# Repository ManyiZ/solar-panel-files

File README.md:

# About
Solar panel designs. HS-2 is designed in KiCAD, older designs are imported files from EasyEDA.

## KiCad Resources
Download: https://www.kicad.org/download/

Docs: https://docs.kicad.org/#_getting_started

## Easy EDA PCB Ordering Resource
https://docs.easyeda.com/en/PCB/Order-PCB

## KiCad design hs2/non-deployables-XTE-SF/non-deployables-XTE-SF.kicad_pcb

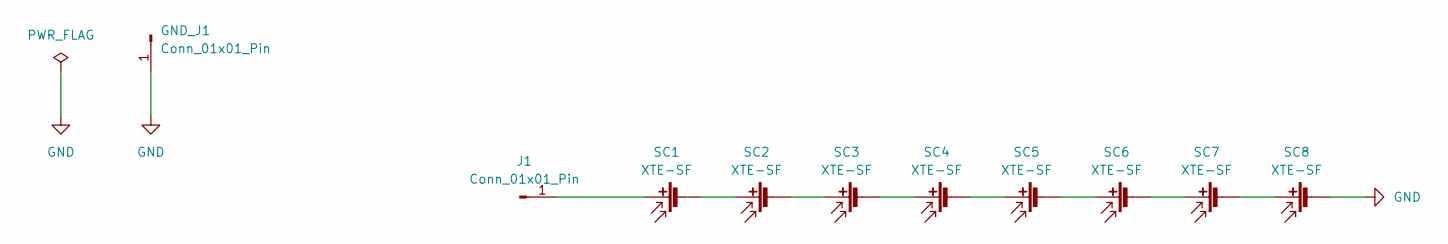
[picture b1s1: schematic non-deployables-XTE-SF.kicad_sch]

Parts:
GND_J1: Conn_01x01_Pin; SolderWirePad_1x01_SMD_5x10mm
J1: Conn_01x01_Pin; SolderWirePad_1x01_SMD_5x10mm
SC1, SC2, SC3, SC4, SC5, SC6, SC7, SC8: XTE-SF; xte-sf

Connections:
GND: GND_J1.1, SC8.2 (-)
unnamed: J1.1, SC1.1 (+)
unnamed: SC1.2 (-), SC2.1 (+)
unnamed: SC2.2 (-), SC3.1 (+)
unnamed: SC3.2 (-), SC4.1 (+)
unnamed: SC4.2 (-), SC5.1 (+)
unnamed: SC5.2 (-), SC6.1 (+)
unnamed: SC6.2 (-), SC7.1 (+)
unnamed: SC7.2 (-), SC8.1 (+)

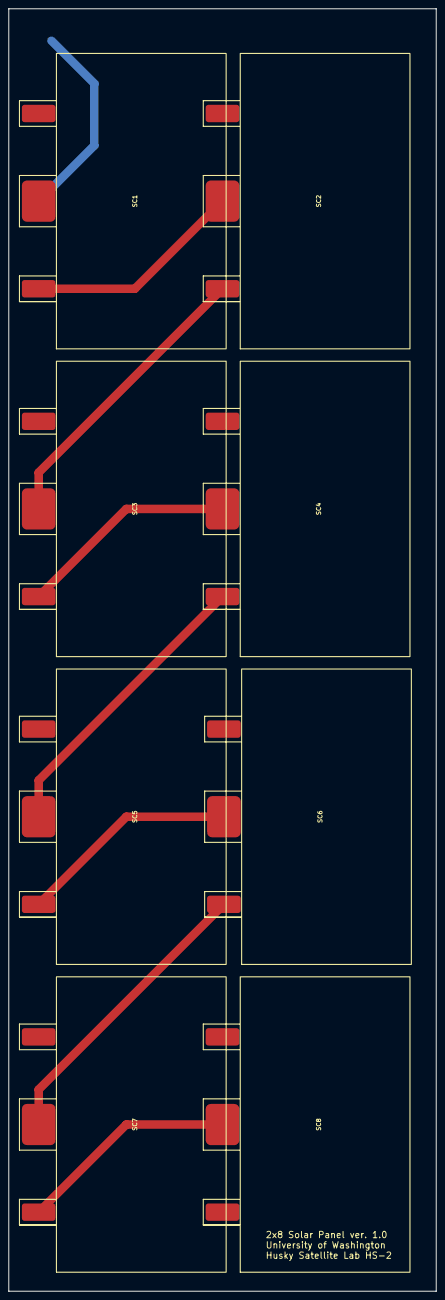
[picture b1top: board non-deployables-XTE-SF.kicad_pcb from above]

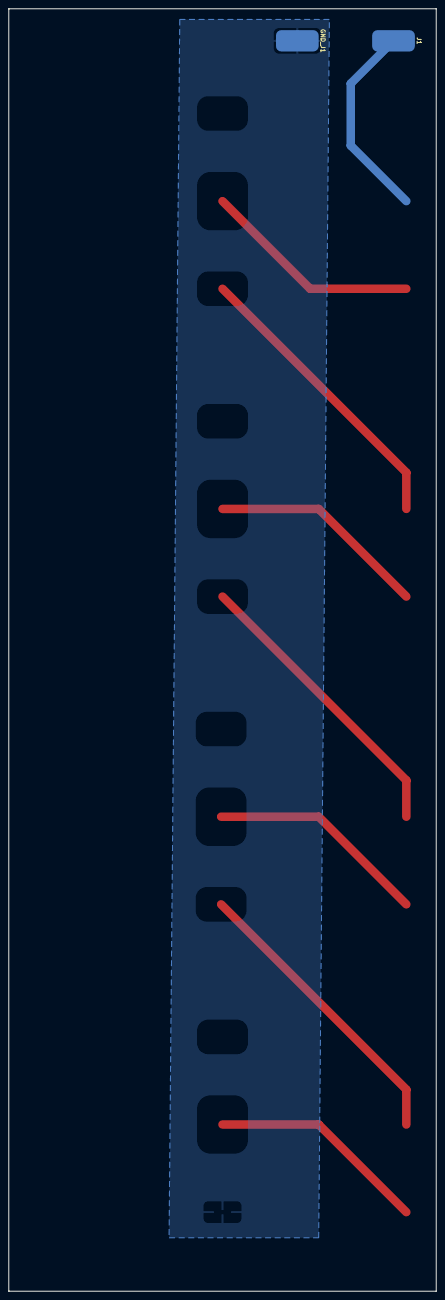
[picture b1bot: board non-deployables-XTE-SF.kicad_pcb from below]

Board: 2 copper layers, 100.0 x 300.0 mm, 10 parts (2 on the bottom side), 9 nets.

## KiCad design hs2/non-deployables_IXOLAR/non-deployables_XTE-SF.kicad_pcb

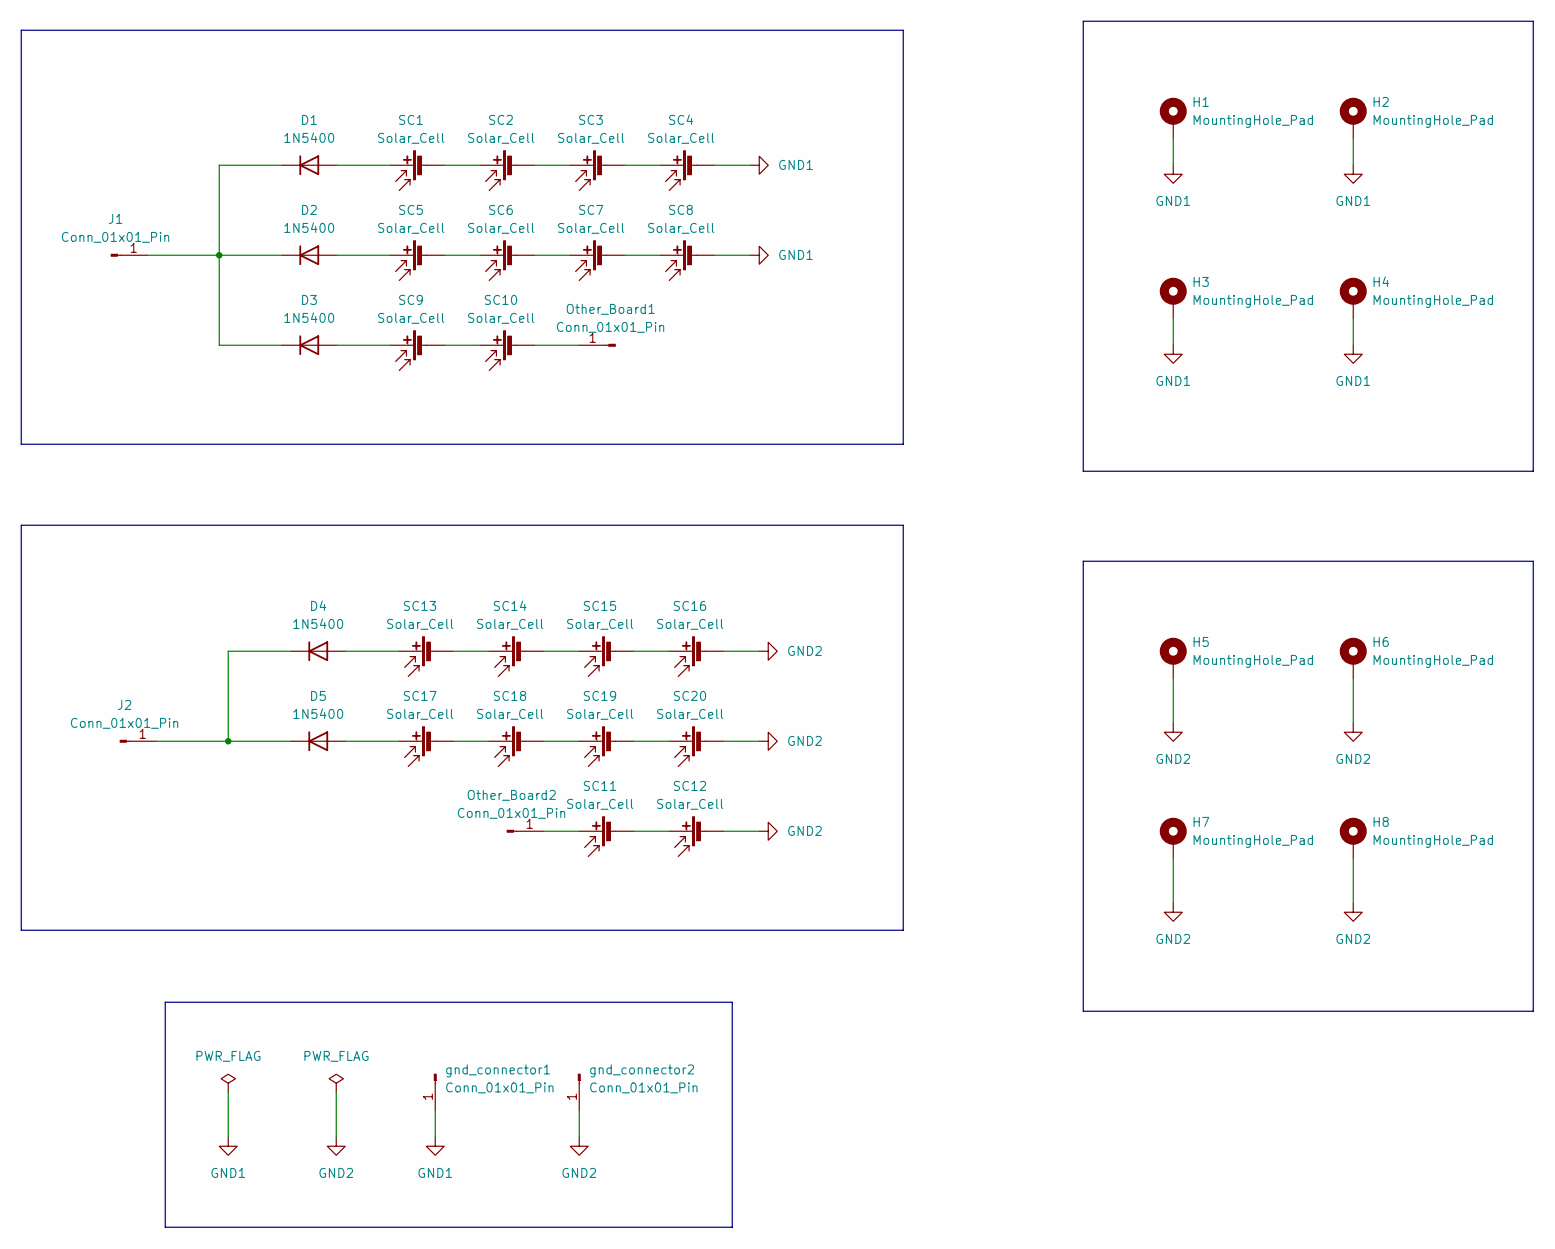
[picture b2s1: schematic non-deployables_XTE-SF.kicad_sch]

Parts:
D1, D2, D3, D4, D5: 1N5400; D_DO-201AD_P15.24mm_Horizontal
H1, H2, H3, H4, H5, H6, H7, H8: MountingHole_Pad; MountingHole_3.2mm_M3_DIN965_Pad
J1, J2: Conn_01x01_Pin; SolderWirePad_1x01_SMD_5x10mm
Other_Board1, Other_Board2: Conn_01x01_Pin; SolderWirePad_1x01_SMD_5x10mm
SC1, SC2, SC3, SC4, SC5, SC6, SC7, SC8, SC9, SC10, SC11, SC12, SC13, SC14, SC15, SC16, SC17, SC18, SC19, SC20: Solar_Cell; XOLAR_SM401K08TF
gnd_connector1, gnd_connector2: Conn_01x01_Pin; SolderWirePad_1x01_SMD_5x10mm

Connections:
GND1: H1.1, H2.1, H3.1, H4.1, SC4.2 (-), SC8.2 (-), gnd_connector1.1
GND2: H5.1, H6.1, H7.1, H8.1, SC12.2 (-), SC16.2 (-), SC20.2 (-), gnd_connector2.1
unnamed: D1.2 (A), SC1.1 (+)
unnamed: D1.1 (K), D2.1 (K), D3.1 (K), J1.1
unnamed: D2.2 (A), SC5.1 (+)
unnamed: D3.2 (A), SC9.1 (+)
unnamed: D4.2 (A), SC13.1 (+)
unnamed: D4.1 (K), D5.1 (K), J2.1
unnamed: D5.2 (A), SC17.1 (+)
unnamed: Other_Board1.1, SC10.2 (-)
unnamed: Other_Board2.1, SC11.1 (+)
unnamed: SC1.2 (-), SC2.1 (+)
unnamed: SC2.2 (-), SC3.1 (+)
unnamed: SC3.2 (-), SC4.1 (+)
unnamed: SC5.2 (-), SC6.1 (+)
unnamed: SC6.2 (-), SC7.1 (+)
unnamed: SC7.2 (-), SC8.1 (+)
unnamed: SC9.2 (-), SC10.1 (+)
unnamed: SC11.2 (-), SC12.1 (+)
unnamed: SC13.2 (-), SC14.1 (+)
unnamed: SC14.2 (-), SC15.1 (+)
unnamed: SC15.2 (-), SC16.1 (+)
unnamed: SC17.2 (-), SC18.1 (+)
unnamed: SC18.2 (-), SC19.1 (+)
unnamed: SC19.2 (-), SC20.1 (+)

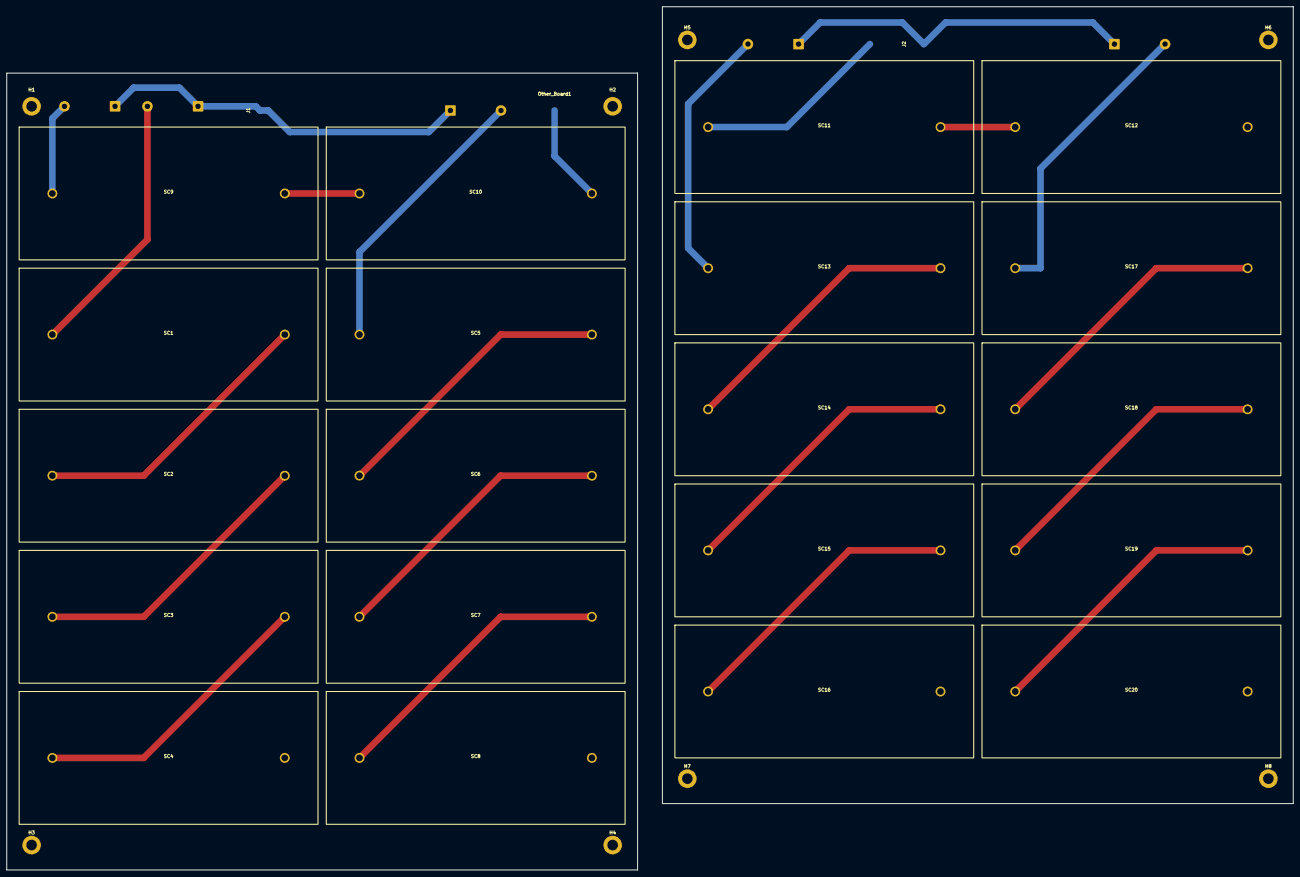
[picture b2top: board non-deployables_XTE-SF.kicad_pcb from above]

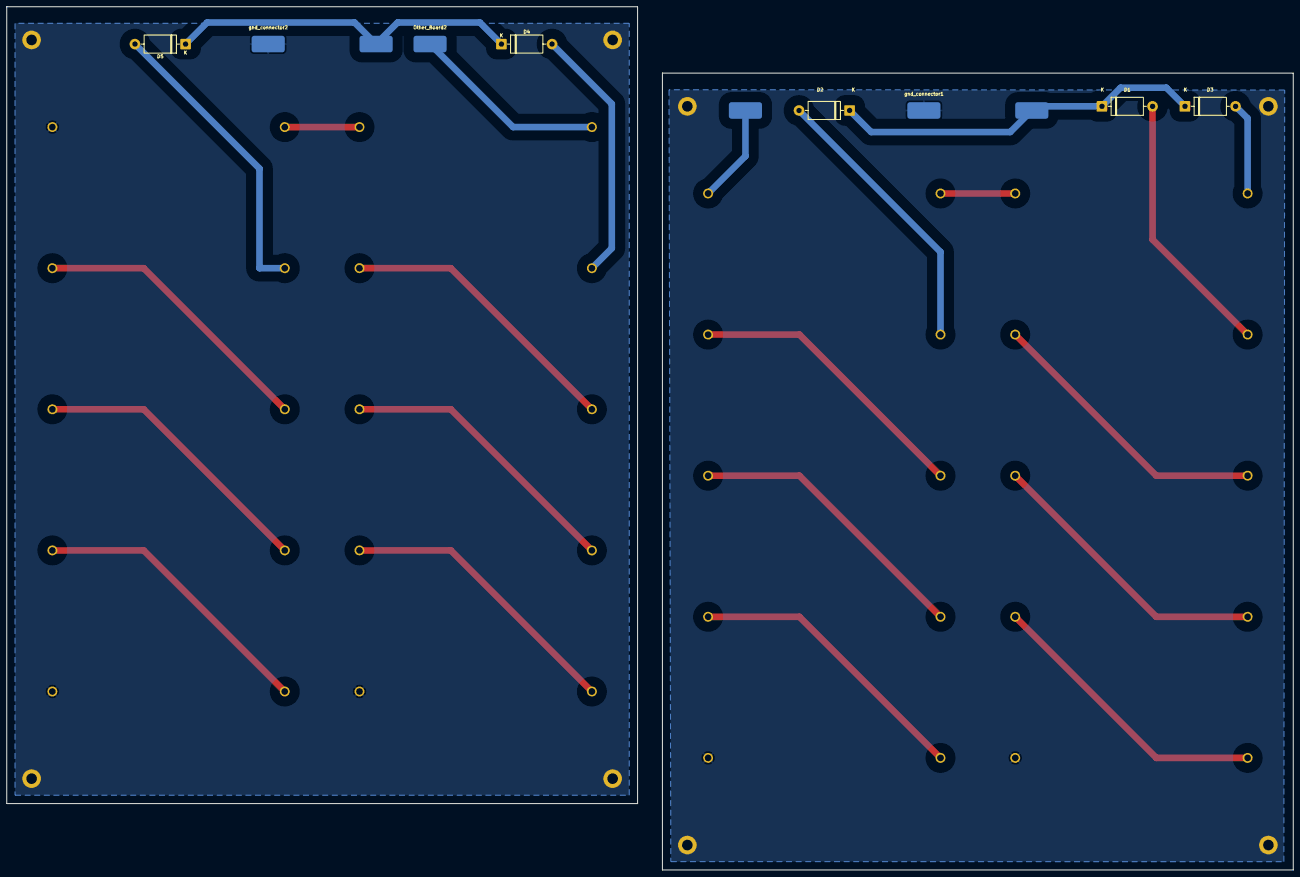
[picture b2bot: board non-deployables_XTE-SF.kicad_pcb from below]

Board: 2 copper layers, 387.5 x 260.0 mm, 39 parts (8 on the bottom side), 25 nets.

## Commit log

2024-11-14 uploaded hs2 pcb cad files
2024-11-14 fixed the order pcb txt file location
2024-11-21 updated stepper files
2025-10-13 prototyping hs2 panels that use xte-sf
2025-10-13 setting up ixolar prototype design
2025-10-13 setting up prototype arrays
2025-10-18 updated schematic
2025-10-18 started prototype pcbs for 2 panel boards
2025-10-18 update prototype pcb
2025-10-18 finished drafting prototype panels
2025-10-18 having problems with smd connectors
2025-10-19 prototype board questionable according to KiCAD :cry:
2025-10-21 ver 1.0 of xte-sf board
2025-10-23 updated ixolar footprints
2025-10-24 updated with mounting holes
2025-10-24 added pcb labels
2025-10-24 changed file names
2025-11-14 added gerber files for prototype
2025-11-14 changed footprints
2026-05-01 started stack KiCAD
2026-05-01 started solar stack
